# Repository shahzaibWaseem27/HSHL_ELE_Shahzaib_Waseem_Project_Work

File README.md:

# HSHL_ELE_Shahzaib_Waseem_Project_Work

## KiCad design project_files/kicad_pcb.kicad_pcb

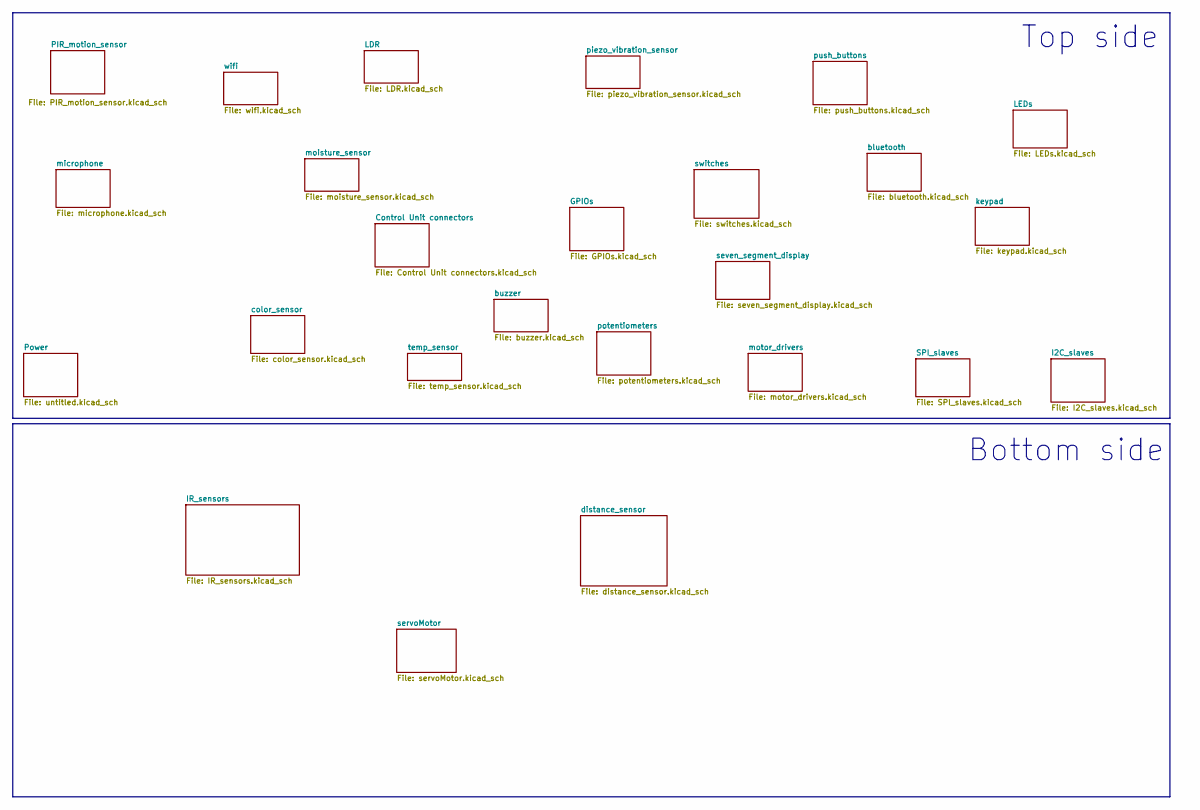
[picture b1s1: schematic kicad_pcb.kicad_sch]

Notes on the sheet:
Bottom side
Top side

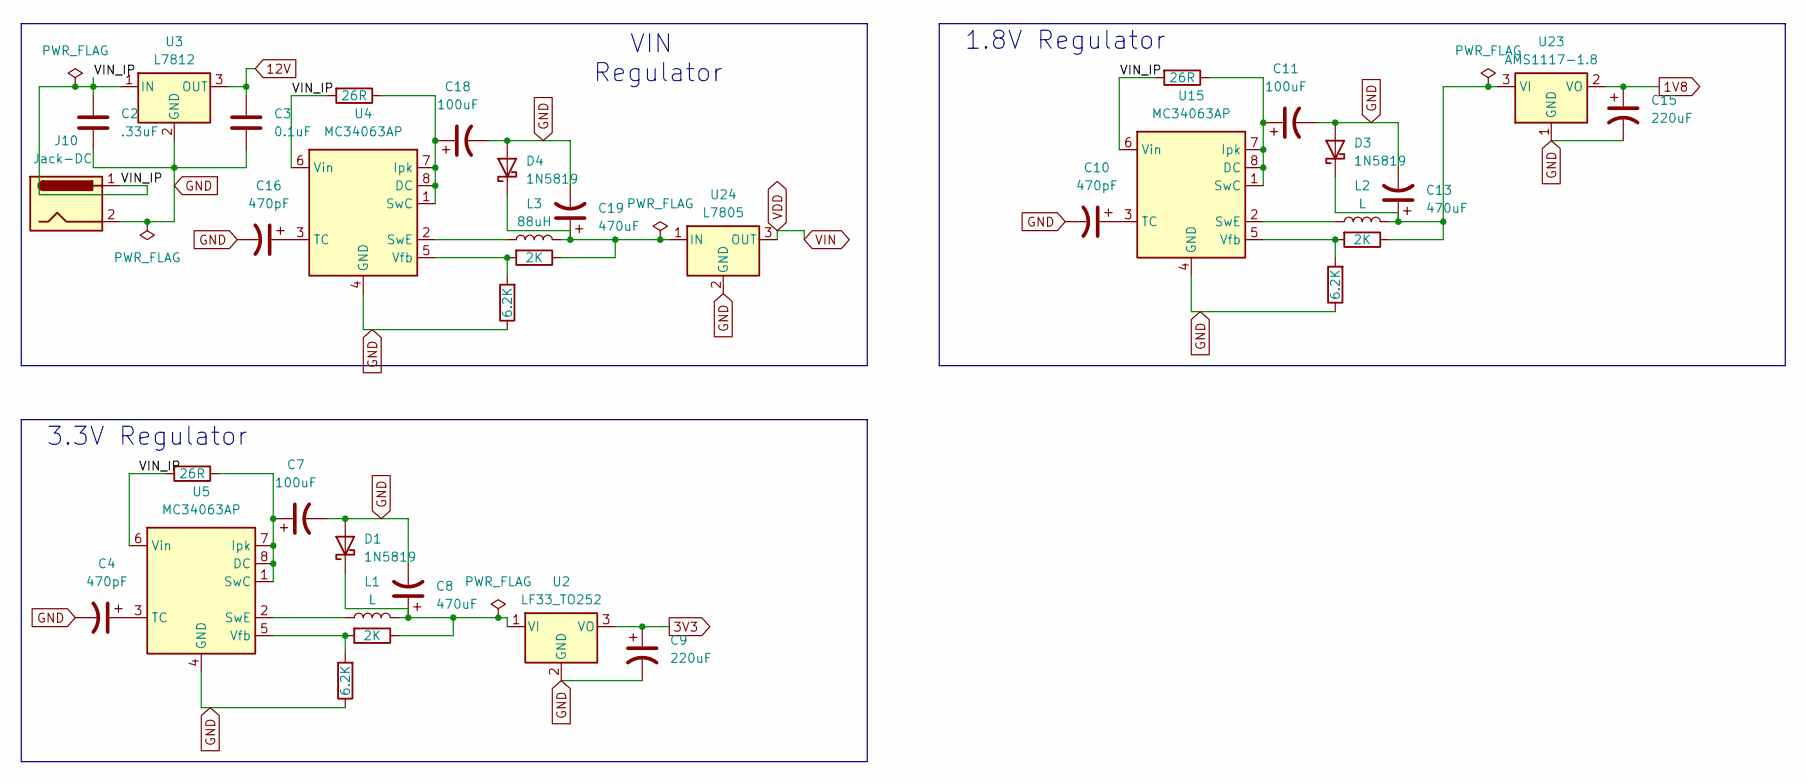
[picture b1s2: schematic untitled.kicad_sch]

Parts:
C2: .33uF; C_0805_2012Metric
C3: 0.1uF; C_0805_2012Metric
C4, C10, C16: 470pF; CP_Elec_3x5.3
C7, C11, C18: 100uF; CP_Elec_6.3x7.7
C8, C13, C19: 470uF; CP_Elec_6.3x7.7
C9, C15: 220uF; CP_Elec_6.3x7.7
D1, D3, D4: 1N5819; D_2114_3652Metric
J10: Jack-DC; BarrelJack_SwitchcraftConxall_RAPC10U_Horizontal
L1, L2: L; L_10.4x10.4_H4.8
L3: 88uH; L_10.4x10.4_H4.8
R2, R6, R9: 26R; R_0603_1608Metric
R4, R7, R10: 6.2K; R_0603_1608Metric
R5, R8, R11: 2K; R_0603_1608Metric
U2: LF33_TO252; TO-252-2
U3: L7812; TO-252-2
U4, U5, U15: MC34063AP; DIP-8_W8.89mm_SMDSocket_LongPads
U23: AMS1117-1.8; SOT-223-3_TabPin2
U24: L7805; TO-252-2

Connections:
1V8: C15.1, U23.2 (VO)
3V3: C9.1, U2.3 (VO); also elsewhere on the board
12V: C3.1, U3.3 (OUT); also elsewhere on the board
/Power/VIN_IP: C2.1, J10.1, R2.2, R6.2, R9.2, U3.1 (IN), U4.6 (Vin), U5.6 (Vin), U15.6 (Vin)
GND: C2.2, C3.2, C4.2, C7.2, C8.2, C9.2, C10.2, C11.2, C13.2, C15.2, C16.2, C18.2, C19.2, D1.2 (A), D3.2 (A), D4.2 (A), J10.2, R4.1, R7.1, R10.1, U2.2 (GND), U3.2 (GND), U4.4 (GND), U5.4 (GND), U15.4 (GND), U23.1 (GND), U24.2 (GND); also elsewhere on the board
unnamed: C8.1, D1.1 (K), L1.2, R5.1, U2.1 (VI)
unnamed: C13.1, D3.1 (K), L2.2, R8.1, U23.3 (VI)
unnamed: C19.1, D4.1 (K), L3.2, R11.1, U24.1 (IN)
unnamed: C18.1, R9.1, U4.1 (SwC), U4.7 (Ipk), U4.8 (DC)
unnamed: L3.1, U4.2 (SwE)
unnamed: C16.1, U4.3 (TC)
unnamed: R10.2, R11.2, U4.5 (Vfb)
unnamed: C7.1, R2.1, U5.1 (SwC), U5.7 (Ipk), U5.8 (DC)
unnamed: L1.1, U5.2 (SwE)
unnamed: C4.1, U5.3 (TC)
unnamed: R4.2, R5.2, U5.5 (Vfb)
unnamed: C11.1, R6.1, U15.1 (SwC), U15.7 (Ipk), U15.8 (DC)
unnamed: L2.1, U15.2 (SwE)
unnamed: C10.1, U15.3 (TC)
unnamed: R7.2, R8.2, U15.5 (Vfb)
VDD: U24.3 (OUT); also elsewhere on the board

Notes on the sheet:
1.8V Regulator
VIN Regulator
3.3V Regulator

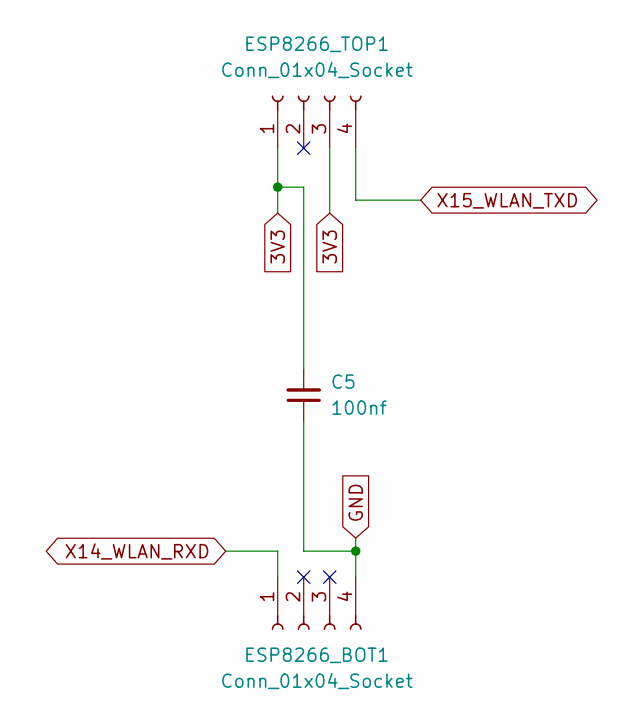
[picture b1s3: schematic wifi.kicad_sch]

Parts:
C5: 100nf; C_0603_1608Metric
ESP8266_BOT1, ESP8266_TOP1: Conn_01x04_Socket; PinSocket_1x04_P2.54mm_Vertical_SMD_Pin1Left

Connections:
3V3: C5.2, ESP8266_TOP1.1, ESP8266_TOP1.3; also elsewhere on the board
GND: C5.1, ESP8266_BOT1.4; also elsewhere on the board
X14_WLAN_RXD: ESP8266_BOT1.1; also elsewhere on the board
X15_WLAN_TXD: ESP8266_TOP1.4; also elsewhere on the board

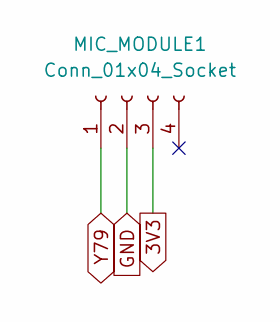
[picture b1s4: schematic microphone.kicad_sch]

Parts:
MIC_MODULE1: Conn_01x04_Socket; PinSocket_1x04_P2.54mm_Vertical_SMD_Pin1Left

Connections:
3V3: MIC_MODULE1.3; also elsewhere on the board
GND: MIC_MODULE1.2; also elsewhere on the board
Y79: MIC_MODULE1.1; also elsewhere on the board

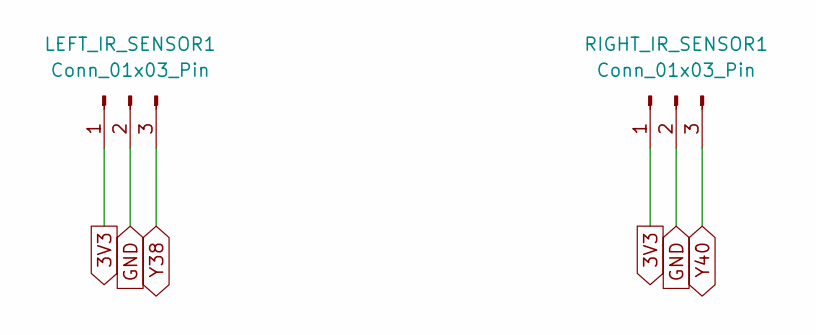
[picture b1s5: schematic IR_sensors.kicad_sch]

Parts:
LEFT_IR_SENSOR1: Conn_01x03_Pin; PinHeader_1x03_P2.54mm_Vertical_SMD_Pin1Left
RIGHT_IR_SENSOR1: Conn_01x03_Pin; PinHeader_1x03_P2.54mm_Vertical_SMD_Pin1Left

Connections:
3V3: LEFT_IR_SENSOR1.1, RIGHT_IR_SENSOR1.1; also elsewhere on the board
GND: LEFT_IR_SENSOR1.2, RIGHT_IR_SENSOR1.2; also elsewhere on the board
Y38: LEFT_IR_SENSOR1.3; also elsewhere on the board
Y40: RIGHT_IR_SENSOR1.3; also elsewhere on the board

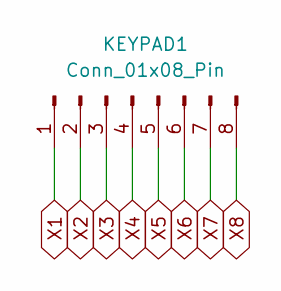
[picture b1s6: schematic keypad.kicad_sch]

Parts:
KEYPAD1: Conn_01x08_Pin; PinHeader_1x08_P2.54mm_Vertical_SMD_Pin1Left

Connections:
X1: KEYPAD1.1; also elsewhere on the board
X2: KEYPAD1.2; also elsewhere on the board
X3: KEYPAD1.3; also elsewhere on the board
X4: KEYPAD1.4; also elsewhere on the board
X5: KEYPAD1.5; also elsewhere on the board
X6: KEYPAD1.6; also elsewhere on the board
X7: KEYPAD1.7; also elsewhere on the board
X8: KEYPAD1.8; also elsewhere on the board

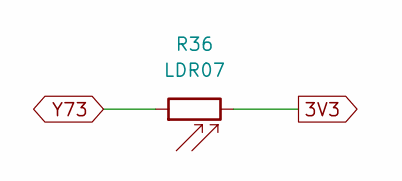
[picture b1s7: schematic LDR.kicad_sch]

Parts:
R36: LDR07; R_LDR_5.1x4.3mm_P3.4mm_Vertical

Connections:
3V3: R36.2; also elsewhere on the board
Y73: R36.1; also elsewhere on the board

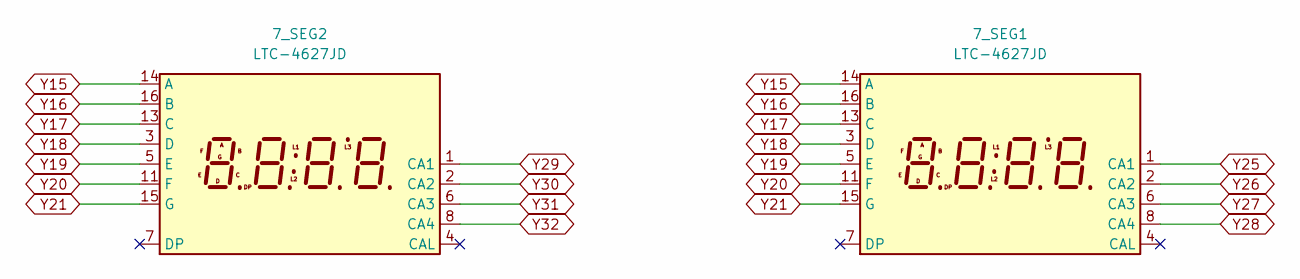
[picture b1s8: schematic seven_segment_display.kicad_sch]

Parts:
7_SEG1, 7_SEG2: LTC-4627JD; LTC-4627Jx

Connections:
Y15: 7_SEG1.14 (A), 7_SEG2.14 (A); also elsewhere on the board
Y16: 7_SEG1.16 (B), 7_SEG2.16 (B); also elsewhere on the board
Y17: 7_SEG1.13 (C), 7_SEG2.13 (C); also elsewhere on the board
Y18: 7_SEG1.3 (D), 7_SEG2.3 (D); also elsewhere on the board
Y19: 7_SEG1.5 (E), 7_SEG2.5 (E); also elsewhere on the board
Y20: 7_SEG1.11 (F), 7_SEG2.11 (F); also elsewhere on the board
Y21: 7_SEG1.15 (G), 7_SEG2.15 (G); also elsewhere on the board
Y25: 7_SEG1.1 (CA1); also elsewhere on the board
Y26: 7_SEG1.2 (CA2); also elsewhere on the board
Y27: 7_SEG1.6 (CA3); also elsewhere on the board
Y28: 7_SEG1.8 (CA4); also elsewhere on the board
Y29: 7_SEG2.1 (CA1); also elsewhere on the board
Y30: 7_SEG2.2 (CA2); also elsewhere on the board
Y31: 7_SEG2.6 (CA3); also elsewhere on the board
Y32: 7_SEG2.8 (CA4); also elsewhere on the board

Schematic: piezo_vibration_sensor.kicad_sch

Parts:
PIEZO_VIBRATION_SENSOR1: Conn_01x03_Socket; PinSocket_1x03_P2.54mm_Vertical_SMD_Pin1Left

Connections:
3V3: PIEZO_VIBRATION_SENSOR1.2; also elsewhere on the board
GND: PIEZO_VIBRATION_SENSOR1.1; also elsewhere on the board
Y74: PIEZO_VIBRATION_SENSOR1.3; also elsewhere on the board

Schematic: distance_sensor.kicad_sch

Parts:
DIST_SENSOR1: Conn_01x04_Socket; PinSocket_1x04_P2.54mm_Vertical_SMD_Pin1Left

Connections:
3V3: DIST_SENSOR1.1; also elsewhere on the board
GND: DIST_SENSOR1.4; also elsewhere on the board
Y59: DIST_SENSOR1.2; also elsewhere on the board
Y76: DIST_SENSOR1.3; also elsewhere on the board

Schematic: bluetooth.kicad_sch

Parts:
HC05_BLE1: Conn_01x06_Socket; PinHeader_1x06_P2.54mm_Vertical_SMD_Pin1Left

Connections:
3V3: HC05_BLE1.5; also elsewhere on the board
GND: HC05_BLE1.4; also elsewhere on the board
X12_BLE_RXD: HC05_BLE1.2; also elsewhere on the board
X13_BLE_TXD: HC05_BLE1.3; also elsewhere on the board

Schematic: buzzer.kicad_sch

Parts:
BUZZER1: Conn_01x03_Socket; PinSocket_1x03_P2.54mm_Vertical_SMD_Pin1Left

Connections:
3V3: BUZZER1.1; also elsewhere on the board
GND: BUZZER1.3; also elsewhere on the board
Y13: BUZZER1.2; also elsewhere on the board

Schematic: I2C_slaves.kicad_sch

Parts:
OLED1: Conn_01x04_Socket; PinSocket_1x04_P2.54mm_Vertical_SMD_Pin1Left

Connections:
3V3: OLED1.2; also elsewhere on the board
GND: OLED1.1; also elsewhere on the board
X44: OLED1.4; also elsewhere on the board
X46: OLED1.3; also elsewhere on the board

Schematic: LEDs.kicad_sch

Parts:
LED_1, LED_2, LED_3, LED_4, LED_5, LED_6, LED_7, LED_8, LED_9, LED_10, LED_11, LED_12, LED_13, LED_14, LED_15, LED_16: LED; LED_0201_0603Metric
R33, R34, R35, R38, R39, R40, R41, R42, R43, R44, R45, R46, R47, R48, R49, R50: 220R; R_0603_1608Metric

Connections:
GND: LED_1.1 (K), LED_2.1 (K), LED_3.1 (K), LED_4.1 (K), LED_5.1 (K), LED_6.1 (K), LED_7.1 (K), LED_8.1 (K), LED_9.1 (K), LED_10.1 (K), LED_11.1 (K), LED_12.1 (K), LED_13.1 (K), LED_14.1 (K), LED_15.1 (K), LED_16.1 (K); also elsewhere on the board
unnamed: LED_1.2 (A), R33.2
unnamed: LED_2.2 (A), R34.2
unnamed: LED_3.2 (A), R35.2
unnamed: LED_4.2 (A), R38.2
unnamed: LED_5.2 (A), R39.2
unnamed: LED_6.2 (A), R40.2
unnamed: LED_7.2 (A), R41.2
unnamed: LED_8.2 (A), R42.2
unnamed: LED_9.2 (A), R43.2
unnamed: LED_10.2 (A), R44.2
unnamed: LED_11.2 (A), R45.2
unnamed: LED_12.2 (A), R46.2
unnamed: LED_13.2 (A), R47.2
unnamed: LED_14.2 (A), R48.2
unnamed: LED_15.2 (A), R49.2
unnamed: LED_16.2 (A), R50.2
X24: R33.1; also elsewhere on the board
X25: R34.1; also elsewhere on the board
X26: R35.1; also elsewhere on the board
X33: R38.1; also elsewhere on the board
X34: R39.1; also elsewhere on the board
X35: R40.1; also elsewhere on the board
X36: R41.1; also elsewhere on the board
X37: R42.1; also elsewhere on the board
X38: R43.1; also elsewhere on the board
X39: R44.1; also elsewhere on the board
X40: R45.1; also elsewhere on the board
X49: R46.1; also elsewhere on the board
X50: R47.1; also elsewhere on the board
X51: R48.1; also elsewhere on the board
X52: R49.1; also elsewhere on the board
Y77: R50.1; also elsewhere on the board

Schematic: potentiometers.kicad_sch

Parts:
POT1: POT_1; Potentiometer_ACP_CA6-VSMD_Vertical
POT2: POT_2; Potentiometer_ACP_CA6-VSMD_Vertical

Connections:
3V3: POT1.1, POT2.1; also elsewhere on the board
GND: POT1.3, POT2.3; also elsewhere on the board
X79: POT1.2; also elsewhere on the board
Y75: POT2.2; also elsewhere on the board

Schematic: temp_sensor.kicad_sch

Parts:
DHT22: Conn_01x04_Socket; PinSocket_1x04_P2.54mm_Vertical_SMD_Pin1Left
R37: 10K; R_0201_0603Metric

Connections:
3V3: DHT22.1, R37.1; also elsewhere on the board
GND: DHT22.4; also elsewhere on the board
Y54: DHT22.2, R37.2; also elsewhere on the board

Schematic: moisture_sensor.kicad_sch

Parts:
MOISTURE_SENSOR1: Conn_01x03_Pin; PinHeader_1x03_P2.54mm_Vertical_SMD_Pin1Left

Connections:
3V3: MOISTURE_SENSOR1.2; also elsewhere on the board
GND: MOISTURE_SENSOR1.3; also elsewhere on the board
Y2: MOISTURE_SENSOR1.1; also elsewhere on the board

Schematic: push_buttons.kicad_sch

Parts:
PUSH_BTN_1, PUSH_BTN_2, PUSH_BTN_3, PUSH_BTN_4, PUSH_BTN_5: SW_Push; SW_Push_SPST_NO_Alps_SKRK
R28, R29, R30, R31, R32: 10K; R_0603_1608Metric

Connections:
3V3: PUSH_BTN_1.2, PUSH_BTN_2.2, PUSH_BTN_3.2, PUSH_BTN_4.2, PUSH_BTN_5.2; also elsewhere on the board
GND: R28.2, R29.2, R30.2, R31.2, R32.2; also elsewhere on the board
X75: PUSH_BTN_1.1, R28.1; also elsewhere on the board
X76: PUSH_BTN_2.1, R29.1; also elsewhere on the board
X77: PUSH_BTN_3.1, R30.1; also elsewhere on the board
X78: PUSH_BTN_4.1, R31.1; also elsewhere on the board
Y78: PUSH_BTN_5.1, R32.1; also elsewhere on the board

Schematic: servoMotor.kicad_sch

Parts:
LEFT_SERVO1: Servo; PinHeader_1x03_P2.54mm_Vertical_SMD_Pin1Left
RIGHT_SERVO1: Servo; PinHeader_1x03_P2.54mm_Vertical_SMD_Pin1Left

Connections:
GND: LEFT_SERVO1.3, RIGHT_SERVO1.3; also elsewhere on the board
VDD: LEFT_SERVO1.1, RIGHT_SERVO1.1; also elsewhere on the board
Y61: LEFT_SERVO1.2; also elsewhere on the board
Y67: RIGHT_SERVO1.2; also elsewhere on the board

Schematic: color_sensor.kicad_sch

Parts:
COLOR_SENSOR_DATA1: Conn_01x05_Socket; PinSocket_1x05_P2.54mm_Vertical_SMD_Pin1Left
COLOR_SENSOR_PWR1: Conn_01x05_Socket; PinSocket_1x05_P2.54mm_Vertical_SMD_Pin1Left

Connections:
3V3: COLOR_SENSOR_PWR1.5; also elsewhere on the board
GND: COLOR_SENSOR_PWR1.1; also elsewhere on the board
Y1: COLOR_SENSOR_DATA1.1; also elsewhere on the board
Y3: COLOR_SENSOR_DATA1.2; also elsewhere on the board
Y4: COLOR_SENSOR_DATA1.3; also elsewhere on the board
Y14: COLOR_SENSOR_DATA1.4; also elsewhere on the board
Y22: COLOR_SENSOR_DATA1.5; also elsewhere on the board

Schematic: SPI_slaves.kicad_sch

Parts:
LORA_USED_PINS1: Conn_01x09_Socket; PinSocket_1x09_P2.54mm_Vertical_SMD_Pin1Left
RFID1: Conn_01x08_Socket; PinSocket_1x08_P2.54mm_Vertical_SMD_Pin1Left

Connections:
3V3: LORA_USED_PINS1.1, RFID1.8; also elsewhere on the board
GND: LORA_USED_PINS1.2, RFID1.6; also elsewhere on the board
X9: LORA_USED_PINS1.5, RFID1.2; also elsewhere on the board
X10: LORA_USED_PINS1.6, RFID1.4; also elsewhere on the board
X11: LORA_USED_PINS1.7, RFID1.3; also elsewhere on the board
Y48: LORA_USED_PINS1.4; also elsewhere on the board
Y49: LORA_USED_PINS1.8; also elsewhere on the board
Y50: LORA_USED_PINS1.9; also elsewhere on the board
Y51: RFID1.1; also elsewhere on the board
Y52: RFID1.7; also elsewhere on the board

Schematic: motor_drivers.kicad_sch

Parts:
LEFT_MOTOR1: Conn_01x02_Pin; PinHeader_1x02_P2.54mm_Vertical_SMD_Pin1Left
RIGHT_MOTOR1: Conn_01x02_Pin; PinHeader_1x02_P2.54mm_Vertical_SMD_Pin1Left
U1: L298N; TO-220-15_P2.54x2.54mm_StaggerOdd_Lead4.58mm_Vertical

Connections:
12V: U1.4 (Vs); also elsewhere on the board
GND: U1.8 (GND); also elsewhere on the board
unnamed: LEFT_MOTOR1.1, U1.3 (OUT2)
unnamed: LEFT_MOTOR1.2, U1.2 (OUT1)
unnamed: RIGHT_MOTOR1.1, U1.14 (OUT4)
unnamed: RIGHT_MOTOR1.2, U1.13 (OUT3)
Y36: U1.7 (IN2); also elsewhere on the board
Y42: U1.12 (IN4); also elsewhere on the board
Y60: U1.5 (IN1); also elsewhere on the board
Y62: U1.6 (EnA); also elsewhere on the board
Y63: U1.10 (IN3); also elsewhere on the board
Y65: U1.11 (EnB); also elsewhere on the board

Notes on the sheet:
DC Motor

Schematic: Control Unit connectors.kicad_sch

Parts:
R12, R14: 2kR; R_0603_1608Metric
X_conns1: 5024308030
Y_conns1: 5024308030

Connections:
3V3: X_conns1.53, X_conns1.64, Y_conns1.23, Y_conns1.34, Y_conns1.43, Y_conns1.69; also elsewhere on the board
5V: R12.1, R14.1
GND: X_conns1.22, X_conns1.31, X_conns1.42, X_conns1.47, X_conns1.54, Y_conns1.24, Y_conns1.33, Y_conns1.44, Y_conns1.57, Y_conns1.70; also elsewhere on the board
VDD: X_conns1.21, X_conns1.32, X_conns1.41, X_conns1.48; also elsewhere on the board
X1: X_conns1.1; also elsewhere on the board
X2: X_conns1.2; also elsewhere on the board
X3: X_conns1.3; also elsewhere on the board
X4: X_conns1.4; also elsewhere on the board
X5: X_conns1.5; also elsewhere on the board
X6: X_conns1.6; also elsewhere on the board
X7: X_conns1.7; also elsewhere on the board
X8: X_conns1.8; also elsewhere on the board
X9: X_conns1.9; also elsewhere on the board
X10: X_conns1.10; also elsewhere on the board
X11: X_conns1.11; also elsewhere on the board
X12_BLE_RXD: X_conns1.12; also elsewhere on the board
X13_BLE_TXD: X_conns1.13; also elsewhere on the board
X14_WLAN_RXD: X_conns1.14; also elsewhere on the board
X15_WLAN_TXD: X_conns1.15; also elsewhere on the board
X16: X_conns1.16; also elsewhere on the board
X17: X_conns1.17; also elsewhere on the board
X18: X_conns1.18; also elsewhere on the board
X19: X_conns1.19; also elsewhere on the board
X24: X_conns1.24; also elsewhere on the board
X25: X_conns1.25; also elsewhere on the board
X26: X_conns1.26; also elsewhere on the board
X27: X_conns1.27; also elsewhere on the board
X28: X_conns1.28; also elsewhere on the board
X29: X_conns1.29; also elsewhere on the board
X30: X_conns1.30; also elsewhere on the board
X33: X_conns1.33; also elsewhere on the board
X34: X_conns1.34; also elsewhere on the board
X35: X_conns1.35; also elsewhere on the board
X36: X_conns1.36; also elsewhere on the board
X37: X_conns1.37; also elsewhere on the board
X38: X_conns1.38; also elsewhere on the board
X39: X_conns1.39; also elsewhere on the board
X40: X_conns1.40; also elsewhere on the board
X44: R12.2, X_conns1.44; also elsewhere on the board
X46: R14.2, X_conns1.46; also elsewhere on the board
X49: X_conns1.49; also elsewhere on the board
X50: X_conns1.50; also elsewhere on the board
X51: X_conns1.51; also elsewhere on the board
X52: X_conns1.52; also elsewhere on the board
X56: X_conns1.56; also elsewhere on the board
X57: X_conns1.57; also elsewhere on the board
X58: X_conns1.58; also elsewhere on the board
X59: X_conns1.59; also elsewhere on the board
X60: X_conns1.60; also elsewhere on the board
X61: X_conns1.61; also elsewhere on the board
X62: X_conns1.62; also elsewhere on the board
X63: X_conns1.63; also elsewhere on the board
X65: X_conns1.65; also elsewhere on the board
X66: X_conns1.66; also elsewhere on the board
X67: X_conns1.67; also elsewhere on the board
X68: X_conns1.68; also elsewhere on the board
X69: X_conns1.69; also elsewhere on the board
X70: X_conns1.70; also elsewhere on the board
X71: X_conns1.71; also elsewhere on the board
X72: X_conns1.72; also elsewhere on the board
X75: X_conns1.75; also elsewhere on the board
X76: X_conns1.76; also elsewhere on the board
X77: X_conns1.77; also elsewhere on the board
X78: X_conns1.78; also elsewhere on the board
X79: X_conns1.79; also elsewhere on the board
Y1: Y_conns1.1; also elsewhere on the board
Y2: Y_conns1.2; also elsewhere on the board
Y3: Y_conns1.3; also elsewhere on the board
Y4: Y_conns1.4; also elsewhere on the board
Y5: Y_conns1.5; also elsewhere on the board
Y6: Y_conns1.6; also elsewhere on the board
Y7: Y_conns1.7; also elsewhere on the board
Y8: Y_conns1.8; also elsewhere on the board
Y9: Y_conns1.9; also elsewhere on the board
Y10: Y_conns1.10; also elsewhere on the board
Y11: Y_conns1.11; also elsewhere on the board
Y12: Y_conns1.12; also elsewhere on the board
Y13: Y_conns1.13; also elsewhere on the board
Y14: Y_conns1.14; also elsewhere on the board
Y15: Y_conns1.15; also elsewhere on the board
Y16: Y_conns1.16; also elsewhere on the board
Y17: Y_conns1.17; also elsewhere on the board
Y18: Y_conns1.18; also elsewhere on the board
Y19: Y_conns1.19; also elsewhere on the board
Y20: Y_conns1.20; also elsewhere on the board
Y21: Y_conns1.21; also elsewhere on the board
Y22: Y_conns1.22; also elsewhere on the board
Y25: Y_conns1.25; also elsewhere on the board
Y26: Y_conns1.26; also elsewhere on the board
Y27: Y_conns1.27; also elsewhere on the board
Y28: Y_conns1.28; also elsewhere on the board
Y29: Y_conns1.29; also elsewhere on the board
Y30: Y_conns1.30; also elsewhere on the board
Y31: Y_conns1.31; also elsewhere on the board
Y32: Y_conns1.32; also elsewhere on the board
Y36: Y_conns1.36; also elsewhere on the board
Y38: Y_conns1.38; also elsewhere on the board
Y40: Y_conns1.40; also elsewhere on the board
Y42: Y_conns1.42; also elsewhere on the board
Y46: Y_conns1.46; also elsewhere on the board
Y48: Y_conns1.48; also elsewhere on the board
Y49: Y_conns1.49; also elsewhere on the board
Y50: Y_conns1.50; also elsewhere on the board
Y51: Y_conns1.51; also elsewhere on the board
Y52: Y_conns1.52; also elsewhere on the board
Y54: Y_conns1.54; also elsewhere on the board
Y59: Y_conns1.59; also elsewhere on the board
Y60: Y_conns1.60; also elsewhere on the board
Y61: Y_conns1.61; also elsewhere on the board
Y62: Y_conns1.62; also elsewhere on the board
Y63: Y_conns1.63; also elsewhere on the board
Y65: Y_conns1.65; also elsewhere on the board
Y67: Y_conns1.67; also elsewhere on the board
Y73: Y_conns1.73; also elsewhere on the board
Y74: Y_conns1.74; also elsewhere on the board
Y75: Y_conns1.75; also elsewhere on the board
Y76: Y_conns1.76; also elsewhere on the board
Y77: Y_conns1.77; also elsewhere on the board
Y78: Y_conns1.78; also elsewhere on the board
Y79: Y_conns1.79; also elsewhere on the board

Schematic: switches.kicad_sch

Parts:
R1, R3, R13, R15, R16, R17, R18, R19, R20, R21, R22, R23, R24, R25, R26, R27: 220R; R_0603_1608Metric
SW1, SW2, SW3, SW4, SW5, SW6, SW7, SW8, SW9, SW10, SW11, SW12, SW13, SW14, SW15, SW16: SW_DIP_x01; SW_DIP_SPSTx01_Slide_6.7x4.1mm_W6.73mm_P2.54mm_LowProfile_J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

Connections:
3V3: SW1.2, SW2.2, SW3.2, SW4.2, SW5.2, SW6.2, SW7.2, SW8.2, SW9.2, SW10.2, SW11.2, SW12.2, SW13.2, SW14.2, SW15.2, SW16.2; also elsewhere on the board
GND: R1.1, R3.1, R13.1, R15.1, R16.1, R17.1, R18.1, R19.1, R20.1, R21.1, R22.1, R23.1, R24.1, R25.1, R26.1, R27.1; also elsewhere on the board
X56: R1.2, SW1.1; also elsewhere on the board
X57: R3.2, SW2.1; also elsewhere on the board
X58: R13.2, SW3.1; also elsewhere on the board
X59: R15.2, SW4.1; also elsewhere on the board
X60: R16.2, SW5.1; also elsewhere on the board
X61: R17.2, SW6.1; also elsewhere on the board
X62: R18.2, SW7.1; also elsewhere on the board
X63: R19.2, SW8.1; also elsewhere on the board
X65: R20.2, SW9.1; also elsewhere on the board
X66: R21.2, SW10.1; also elsewhere on the board
X67: R22.2, SW11.1; also elsewhere on the board
X68: R23.2, SW12.1; also elsewhere on the board
X69: R24.2, SW13.1; also elsewhere on the board
X70: R25.2, SW14.1; also elsewhere on the board
X71: R26.2, SW15.1; also elsewhere on the board
X72: R27.2, SW16.1; also elsewhere on the board

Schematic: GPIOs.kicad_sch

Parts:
GPIOs1: Conn_01x16_Socket; PinSocket_1x16_P2.54mm_Vertical_SMD_Pin1Left

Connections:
X16: GPIOs1.1; also elsewhere on the board
X17: GPIOs1.2; also elsewhere on the board
X18: GPIOs1.3; also elsewhere on the board
X19: GPIOs1.4; also elsewhere on the board
X27: GPIOs1.5; also elsewhere on the board
X28: GPIOs1.6; also elsewhere on the board
X29: GPIOs1.7; also elsewhere on the board
X30: GPIOs1.8; also elsewhere on the board
Y5: GPIOs1.9; also elsewhere on the board
Y6: GPIOs1.10; also elsewhere on the board
Y7: GPIOs1.11; also elsewhere on the board
Y8: GPIOs1.12; also elsewhere on the board
Y9: GPIOs1.13; also elsewhere on the board
Y10: GPIOs1.14; also elsewhere on the board
Y11: GPIOs1.15; also elsewhere on the board
Y12: GPIOs1.16; also elsewhere on the board

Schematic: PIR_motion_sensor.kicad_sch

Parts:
PIR_MOTION_SENSOR1: Conn_01x03_Socket; PinSocket_1x03_P2.54mm_Vertical_SMD_Pin1Left

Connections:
3V3: PIR_MOTION_SENSOR1.3; also elsewhere on the board
GND: PIR_MOTION_SENSOR1.1; also elsewhere on the board
Y46: PIR_MOTION_SENSOR1.2; also elsewhere on the board

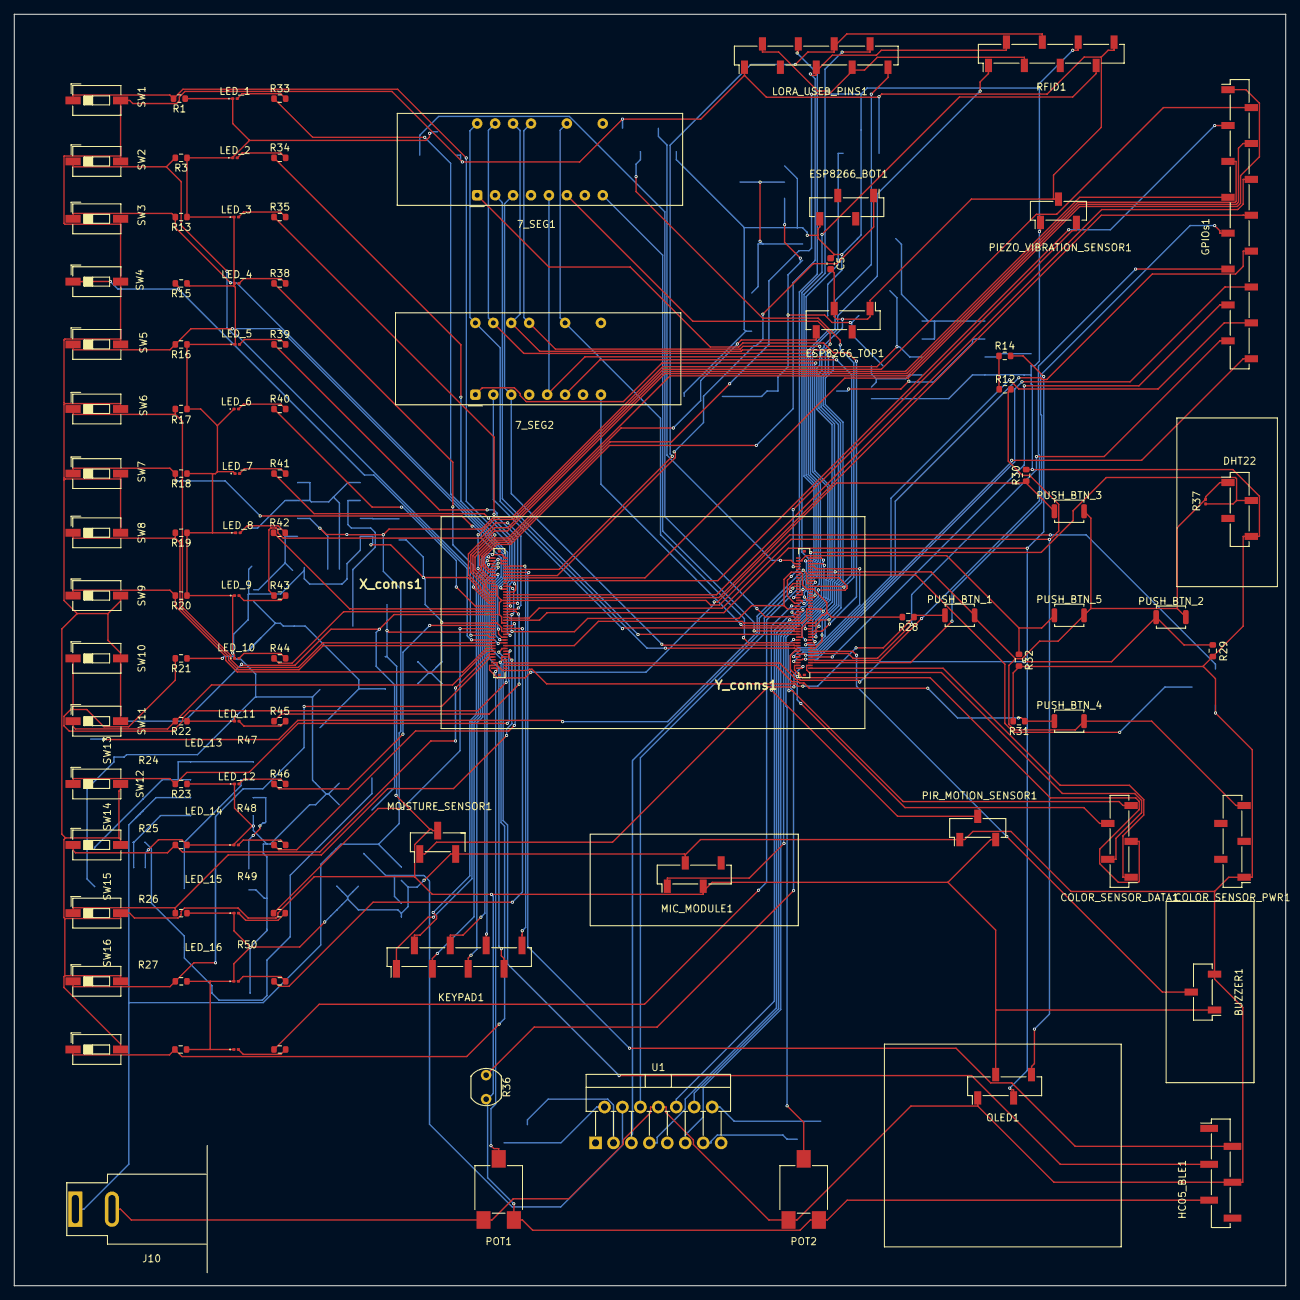
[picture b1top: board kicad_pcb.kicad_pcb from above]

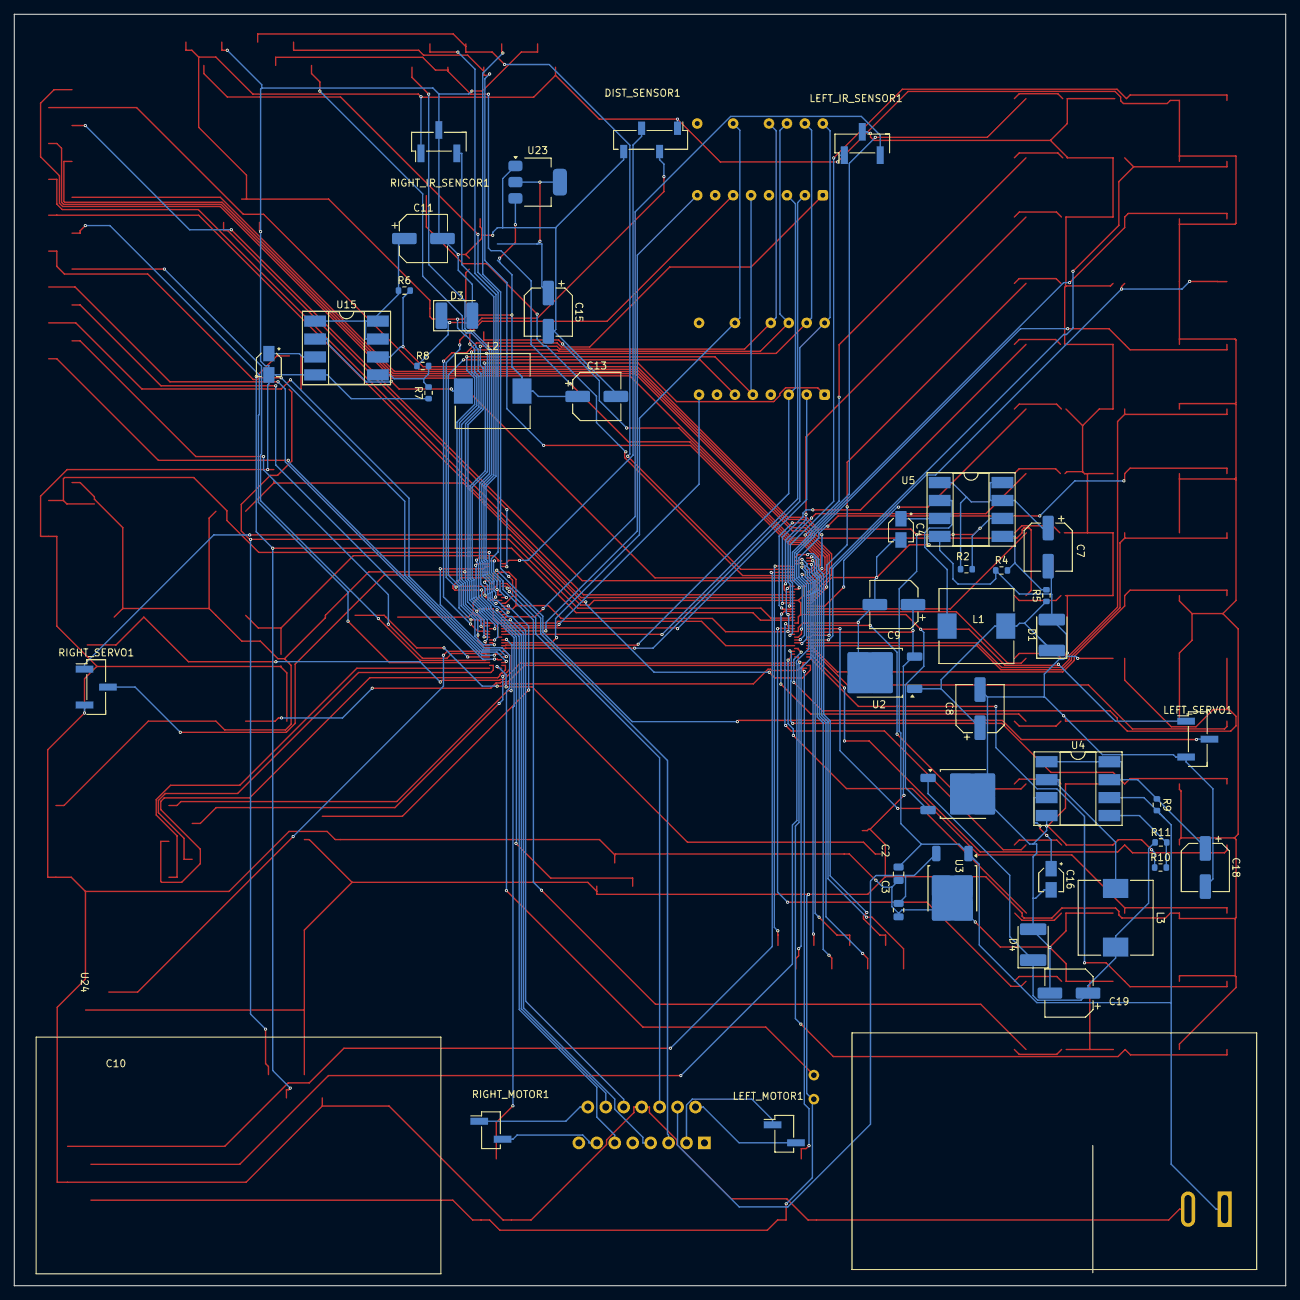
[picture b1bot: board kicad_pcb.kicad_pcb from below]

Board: 2 copper layers, 179.9 x 179.9 mm, 145 parts (42 on the bottom side), 158 nets.

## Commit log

2024-08-13 Add files via upload
    Original project work documentation an project files
2025-01-22 added all macbook files in repo
2025-01-22 Moved previous student files into his folder. Renamed folder
2025-01-22 Added a excel file copy of high density pin connectors pin mapping
2025-02-12 added gerber and drill files
2025-02-13 added latest project work documentation
2025-02-13 fixed incorrect figure numbers in paragraphs mentioning said figures
